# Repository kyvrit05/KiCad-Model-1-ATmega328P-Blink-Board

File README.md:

# 🔧 KiCad Model 1 — ATmega328P Blink Board

As part of strengthening my fundamentals in PCB design and modelling, I started with a simple introductory project: designing a PCB that allows an LED to blink.
Reference Guide from https://www.youtube.com/@HTMWorkshop

The project focuses on understanding the basic PCB design workflow, including schematic creation, component selection, circuit layout, routing, and preparing the board for fabrication. Although the circuit itself is simple, it provides a practical foundation for developing essential PCB design skills and understanding how electronic components are translated from a schematic into a physical PCB.

---

## ⌨️ Shortcuts

| Key | Action |
|-----|--------|
| `A` | Bring up circuit components |
| `P` | Power and GND components |
| `V` | Input a value to a component |
| `R` | Rotate a component by 90° |
| `D` | Move around wires & rearrange |

---

## 📖 Abbreviations

| Term | Meaning |
|------|---------|
| **ERC** | Electrical Rules Checker |
| **THT** | Through-Hole (for soldering back of the PCB) |
| **SMD** | Surface-Mount (no holes on PCB) |
| **ESR** | Equivalent Series Resistance (internal resistance in a component) |

---

## 💡 Key Points

- **Vias** — a small hole that connects front & back layers of the PCB
- **Track size** — a larger track size is for components that require more power, so it's ideal to increase the wiring size
- **Rat's nest** — the connection lines from one component to another

---

## 📷 Progress Outcome Screenshots
p.s find my cute logo in the design ~

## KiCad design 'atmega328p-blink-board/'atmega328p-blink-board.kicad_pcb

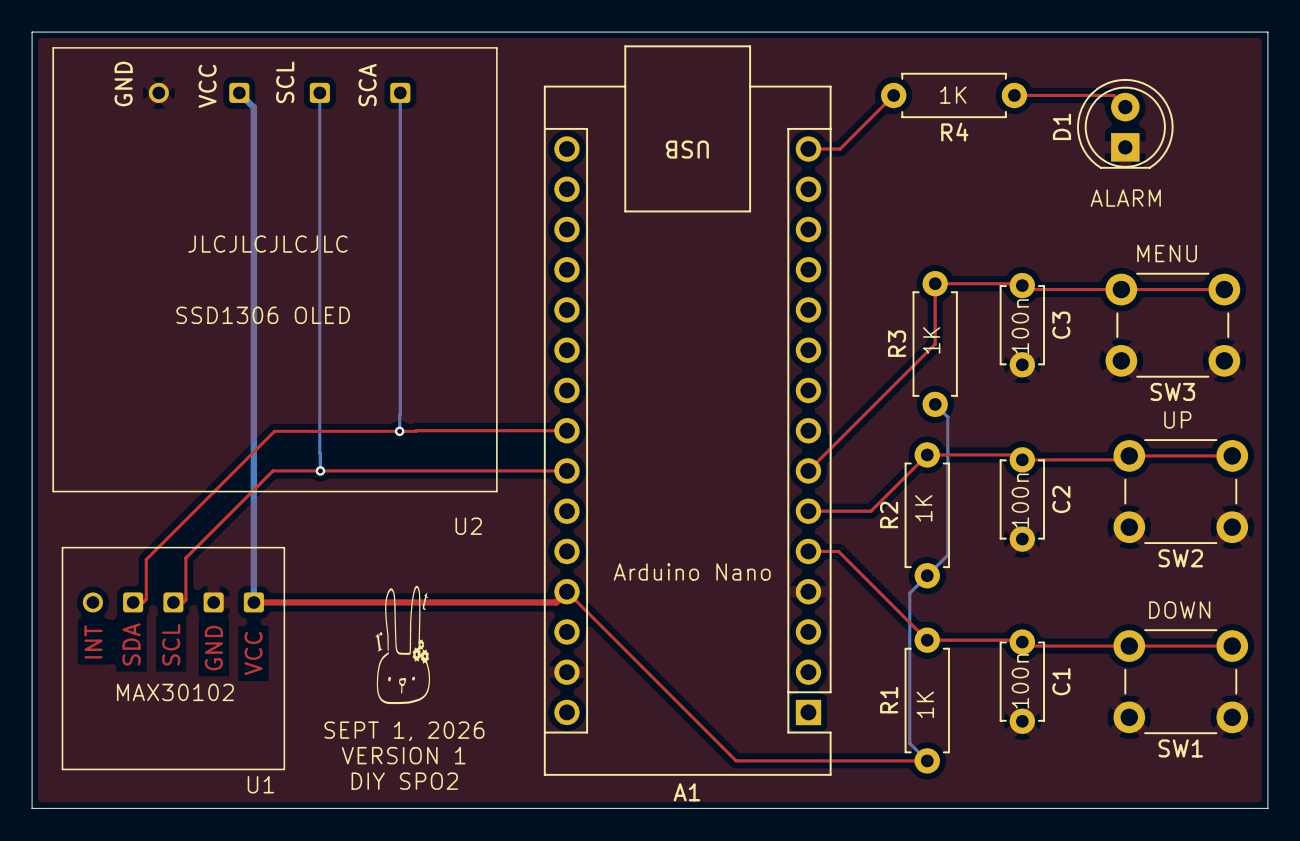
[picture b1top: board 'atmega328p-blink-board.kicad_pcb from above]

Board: 4 copper layers, 78.0 x 49.0 mm, 14 parts (0 on the bottom side), 9 nets.

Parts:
A1: Arduino_Nano_v3.x; Arduino_Nano
C1, C2, C3: 100n; C_Disc_D4.7mm_W2.5mm_P5.00mm
D1: ALARM; LED_D5.0mm
R1, R2, R3: 1K; R_Axial_DIN0207_L6.3mm_D2.5mm_P7.62mm_Horizontal
R4: 1k; R_Axial_DIN0207_L6.3mm_D2.5mm_P7.62mm_Horizontal
SW1: DOWN; SW_PUSH_6mm
SW2: UP; SW_PUSH_6mm
SW3: MENU; SW_PUSH_6mm
U1: MAX30102; MAX30102_MODULE
U2: SSD1306

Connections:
+5V: A1.27 (+5V), R1.1, R2.1, R3.1, U1.5 (VCC), U2.2 (VCC)
GND: A1.4 (GND), A1.29 (GND), C1.2, C2.2, C3.2, D1.1 (K), SW1.1, SW2.1, SW3.1, U1.4 (GND), U2.1 (GND)
unnamed: A1.23 (A4), U1.2 (SDA), U2.4 (SDA)
unnamed: A1.24 (A5), U1.3 (SCL), U2.3 (SCL)
unnamed: A1.5 (D2), C1.1, R1.2, SW1.2
unnamed: A1.6 (D3), C2.1, R2.2, SW2.2
unnamed: A1.7 (D4), C3.1, R3.2, SW3.2
unnamed: A1.15 (D12), R4.2
unnamed: D1.2 (A), R4.1
